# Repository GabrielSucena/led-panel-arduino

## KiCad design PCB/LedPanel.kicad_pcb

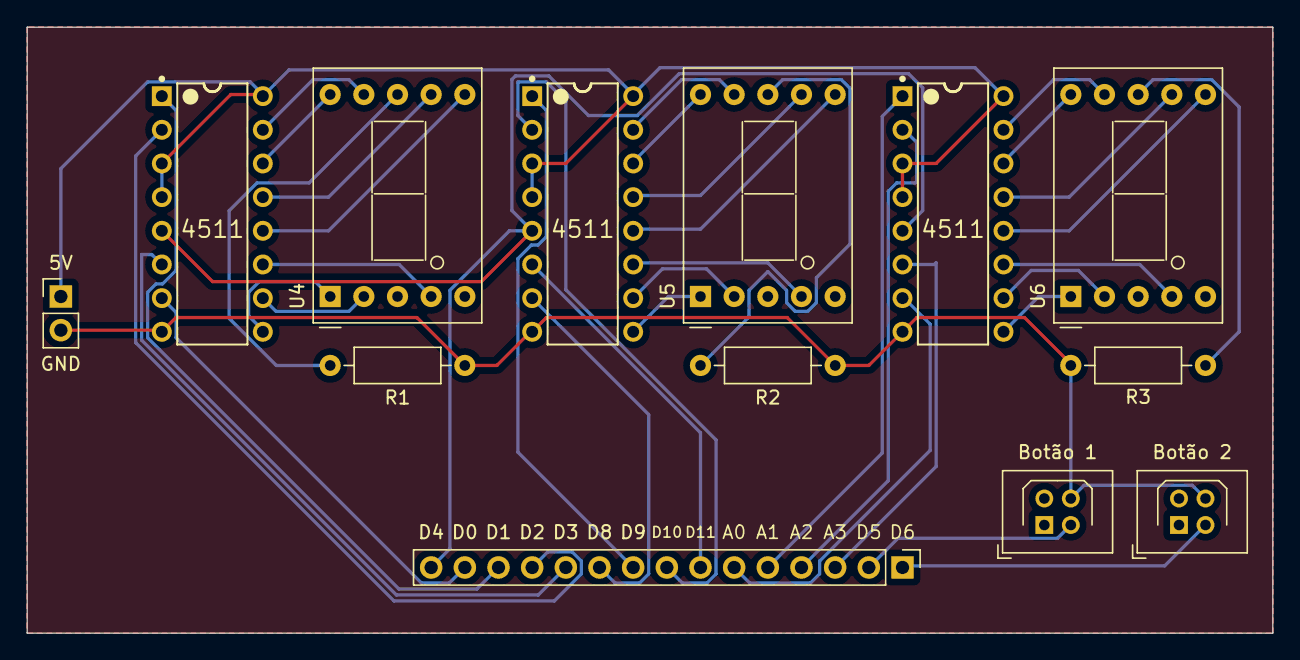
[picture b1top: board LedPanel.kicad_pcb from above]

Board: 2 copper layers, 94.0 x 45.7 mm, 13 parts (0 on the bottom side), 41 nets.

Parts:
Botão 1, Botão 2: Conn_02x02_Top_Bottom; Harwin_LTek-Male_2x02_P2.00mm_Vertical
J1: Conn_01x02_Socket; PinHeader_1x02_P2.54mm_Vertical
J2: Conn_01x15_Socket; PinHeader_1x15_P2.54mm_Vertical
R1, R2, R3: 1K; R_Axial_DIN0207_L6.3mm_D2.5mm_P10.16mm_Horizontal
U1, U2, U3: 4511; Texas_Instruments-CD74HCT4511E-Manufacturer_Recommended
U4, U5, U6: D168K; D1X8K

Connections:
unnamed: J1.1, U1.3 (~LT), U1.4 (~BI), U1.16 (Vdd), U2.3 (~LT), U2.4 (~BI), U2.16 (Vdd), U3.3 (~LT), U3.4 (~BI), U3.16 (Vdd)
unnamed: Botão 1.4, Botão 2.4, J1.2, R1.2, R2.2, R3.2, U1.8 (Vss), U2.8 (Vss), U3.8 (Vss)
unnamed: Botão 2.3, J2.1
unnamed: Botão 1.3, J2.2
unnamed: J2.3, U3.6 (DD)
unnamed: J2.4, U3.2 (DC)
unnamed: J2.5, U3.1 (DB)
unnamed: J2.6, U3.7 (DA)
unnamed: J2.7, U2.6 (DD)
unnamed: J2.8, U2.2 (DC)
unnamed: J2.9, U2.1 (DB)
unnamed: J2.10, U2.7 (DA)
unnamed: J2.11, U1.6 (DD)
unnamed: J2.12, U1.2 (DC)
unnamed: J2.13, U1.1 (DB)
unnamed: J2.14, U1.7 (DA)
unnamed: J2.15, U1.5 (~EL), U2.5 (~EL), U3.5 (~EL)
unnamed: R1.1, U4.8 (CC)
unnamed: R2.1, U5.8 (CC)
unnamed: R3.1, U6.8 (CC)
unnamed: U1.13 (Qa), U4.7 (A)
unnamed: U1.12 (Qb), U4.6 (B)
unnamed: U1.11 (Qc), U4.4 (C)
unnamed: U1.10 (Qd), U4.2 (D)
unnamed: U1.9 (Qe), U4.1 (E)
unnamed: U1.15 (Qf), U4.9 (F)
unnamed: U1.14 (Qg), U4.10 (G)
unnamed: U2.13 (Qa), U5.7 (A)
unnamed: U2.12 (Qb), U5.6 (B)
unnamed: U2.11 (Qc), U5.4 (C)
unnamed: U2.10 (Qd), U5.2 (D)
unnamed: U2.9 (Qe), U5.1 (E)
unnamed: U2.15 (Qf), U5.9 (F)
unnamed: U2.14 (Qg), U5.10 (G)
unnamed: U3.13 (Qa), U6.7 (A)
unnamed: U3.12 (Qb), U6.6 (B)
unnamed: U3.11 (Qc), U6.4 (C)
unnamed: U3.10 (Qd), U6.2 (D)
unnamed: U3.9 (Qe), U6.1 (E)
unnamed: U3.15 (Qf), U6.9 (F)
unnamed: U3.14 (Qg), U6.10 (G)

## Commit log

2023-06-28 Finished Project
